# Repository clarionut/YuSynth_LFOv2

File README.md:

# YuSynth_LFOv2

My modifications to the [YuSynth LFO version #2](http://yusynth.net/Modular/EN/LFO/VC-LFO2.html).

Alterations include
- changes to some component values to reduce current draw
- an increase in the pulse width range to allow very short (or long) pulses
- a fix for glitches in the pulse wave output at low (< 1-2Hz) frequencies
- a modification of the [fix by Gabbagabi](https://electro-music.com/forum/viewtopic.php?t=69587) for problems adjusting the triangle and sine wave symmetry at both high and low frequency settings
- elimination of the 741 op-amp, replaced by the 'spare' TL074

I recently built a second YuSynth LFOv2 for my DIY modular synthesiser. Having installed ammeters in the synth power supply I've become increasingly conscious of high current draw from some modules, and so modified some of the component values to help reduce this, possibly at the expense of some loss of linearity in the control potentiometers (though I haven't noticed this). I also wanted to be able to produce much shorter pulses than the 20-80% duty cycle range of the original. In both of these modules I eliminated the 741 in the rate/modulation input circuitry, instead using the spare op-amp in one of the TL074s (IC3a in the original circuit).

I found that both modules suffered the problem that it was impossible to set the sine and triangle wave symmetry for both the fast and slow speed settings (selected by switching between two different capacitor values). I eventually found the very clever solution by Gabbagabi on the electro-music.com forum (link above). This allows the gain of the fast and slow settings to be adjusted independently, allowing the symmetry to be adjusted for both speed settings. I fixed both my LFOs using a small daughter board for the extra components. The schematic and proposed PCB layout include these in the design, but do note that I have NOT built an LFO using this exact board layout - please check it carefully if you decide to use it!

An additional issue encountered using the pulse wave output as a sequencer clock was that at low frequencies (less that 1-2Hz) the sequencer would occasionally skip steps. Checking the output on a 'scope showed noise pulses at the start of the high phase of the pulse as the comparator (IC2c in the YuSynth original, U2D in my schematic) switched. Adding a high value positive feedback resistor on this comparator gave very clean switching and no more skipped steps from the sequencer.

The original YuSynth schematic includes a ramp (inverted sawtooth) output via R18 (on the YuSynth schematic, R24 here). I included this output on my PCB design, but didn't connect it to the panel. It is available if required though.

This is the new procedure for trimming the triangle/sine wave outputs:
- switch the LFO to the FAST (x1) setting
- monitor the TRIANGLE output with a 'scope
- adjust the FAST SAW BIAS trimmer to get a good symmetrical triangle wave
- adjust the SINE/TRI SYM trimmer to remove any DC offset
- check the SINE output is also symmetrical at this point
- switch the LFO to the SLOW (x10) setting and monitor the triangle output
- iteratively adjust the SLOW SAW BIAS and SLOW GAIN trimmers to get a good triangle wave with no DC offset. These trimmers interact with each other, so make small adjustments to be sure you're going the right way. Do NOT touch the SINE/TRI SYM trimmer during this process.

If there's an extreme imbalance between the FAST and SLOW settings you may need to adjust the value of R18 as well.

The kiCad schematic and PCB design use some custom symbols and footprints, so you may need to include the contents of my [kiCad_libraries repository](https://github.com/clarionut/kiCad_libraries).

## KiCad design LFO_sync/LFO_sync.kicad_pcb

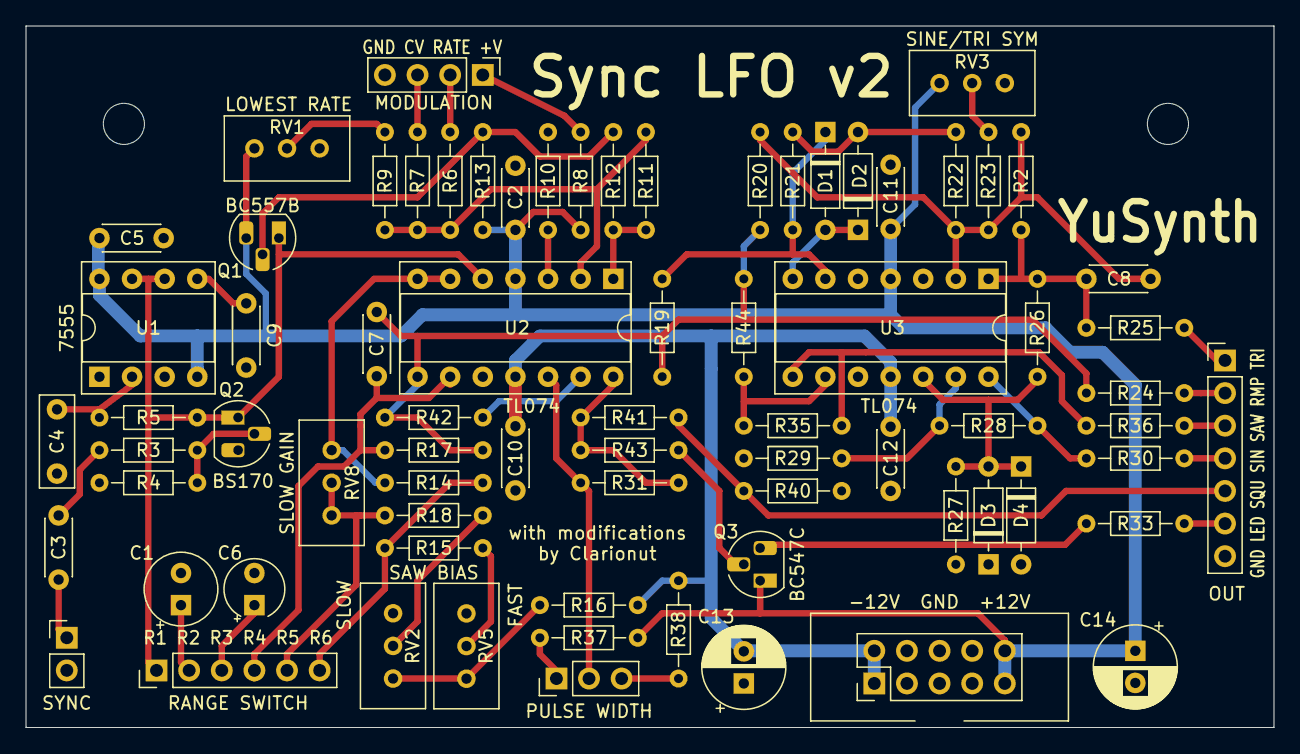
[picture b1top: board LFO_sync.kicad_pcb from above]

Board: 2 copper layers, 97.2 x 54.6 mm, 75 parts (0 on the bottom side), 51 nets.

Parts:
C1: 10u; CP_Radial_Tantal_D5.5mm_P2.50mm
C2, C5, C10, C11, C12: 100n; C_Disc_D4.3mm_W1.9mm_P5.00mm
C3, C9: 10n; C_Disc_D4.3mm_W1.9mm_P5.00mm
C4: 47n; C_Rect_L7.0mm_W2.5mm_P5.00mm
C6: 1u; CP_Radial_Tantal_D4.5mm_P2.50mm
C7: 120p; C_Disc_D4.3mm_W1.9mm_P5.00mm
C8: 1n; C_Disc_D4.3mm_W1.9mm_P5.00mm
C13, C14: 10u; CP_Radial_D6.3mm_P2.50mm
D1, D2, D3, D4: 1N4148; D_DO-35_SOD27_P7.62mm_Horizontal
J1: MODULATION; PinHeader_1x04_P2.54mm_Vertical
J2: SYNC; PinHeader_1x02_P2.54mm_Vertical
J3: RANGE; PinHeader_1x06_P2.54mm_Vertical
J4: PULSE WIDTH; PinHeader_1x03_P2.54mm_Vertical
J7: OUTPUTS; PinHeader_1x07_P2.54mm_Vertical
J8: POWER; Power_2x05
Q1: BC557B; TO-92_HandSolder
Q2: BS170; TO-92_HandSolder
Q3: BC547C; TO-92_HandSolder
R2: 200k; R_Axial_DIN0204_L3.6mm_D1.6mm_P7.62mm_Horizontal
R3, R41, R42: 10k; R_Axial_DIN0204_L3.6mm_D1.6mm_P7.62mm_Horizontal
R4, R6, R7, R9, R11, R14, R15, R19, R20, R21, R33, R35, R44: 100k; R_Axial_DIN0204_L3.6mm_D1.6mm_P7.62mm_Horizontal
R5, R24, R25, R36: 1k; R_Axial_DIN0204_L3.6mm_D1.6mm_P7.62mm_Horizontal
R8: 12k; R_Axial_DIN0204_L3.6mm_D1.6mm_P7.62mm_Horizontal
R10: 8k2; R_Axial_DIN0204_L3.6mm_D1.6mm_P7.62mm_Horizontal
R12, R16: 27k; R_Axial_DIN0204_L3.6mm_D1.6mm_P7.62mm_Horizontal
R13: 820R; R_Axial_DIN0204_L3.6mm_D1.6mm_P7.62mm_Horizontal
R17, R23, R26: 150k; R_Axial_DIN0204_L3.6mm_D1.6mm_P7.62mm_Horizontal
R18, R43: 47k; R_Axial_DIN0204_L3.6mm_D1.6mm_P7.62mm_Horizontal
R22: 50k; R_Axial_DIN0204_L3.6mm_D1.6mm_P7.62mm_Horizontal
R27: 22k; R_Axial_DIN0204_L3.6mm_D1.6mm_P7.62mm_Horizontal
R28: 15k; R_Axial_DIN0204_L3.6mm_D1.6mm_P7.62mm_Horizontal
R29: 1k5; R_Axial_DIN0204_L3.6mm_D1.6mm_P7.62mm_Horizontal
R30: 470R; R_Axial_DIN0204_L3.6mm_D1.6mm_P7.62mm_Horizontal
R31: 3M3; R_Axial_DIN0204_L3.6mm_D1.6mm_P7.62mm_Horizontal
R37, R38: 56k; R_Axial_DIN0204_L3.6mm_D1.6mm_P7.62mm_Horizontal
R40: 7k5; R_Axial_DIN0204_L3.6mm_D1.6mm_P7.62mm_Horizontal
RV1, RV3: 50k; Potentiometer_Bourns_3296W_Vertical
RV2, RV5, RV8: 100k; Potentiometer_Bourns_3296W_Vertical
U1: ICM7555xP; DIP-8_W7.62mm_Socket
U2, U3: TL074; DIP-14_W7.62mm_Socket

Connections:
+12V: C2.1, C5.2, C11.2, C14.1, J8.9, J8.10, Q1.3 (E), Q3.1 (C), R8.1, R13.1, R37.1, RV1.3, RV3.1, U1.4 (R), U1.8 (VCC), U2.4 (V+), U3.4 (V+)
-12V: C10.1, C12.2, C13.2, J8.1, J8.2, R16.1, R38.1, U2.11 (V-), U3.11 (V-)
/+V_RATE: J1.1, R8.2
/CV_MOD: J1.3, R7.2
/LED: J7.6, R33.1
/PULSE: J7.5, R40.1, R41.1
/PW1: J4.1, R37.2
/PW2: J4.2, R31.2, U2.12 (+)
/PW3: J4.3, R38.2
/R1: J3.1, Q1.1 (C), Q2.1 (D), R5.2, U1.6 (THR), U1.7 (DIS), U2.5 (+)
/R2: C1.1, J3.2
/R3: C6.1, J3.3
/R4: C7.2, J3.4, R17.2, U2.9 (-)
/R5: J3.6, R14.2, R15.2
/R6: J3.5, R18.2, RV8.2, RV8.3
/RAMP: J7.2, R24.1
/RATE: J1.2, R6.2
/SAW: J7.3, R36.1
/SINE: J7.4, R30.1
/SYNC: C3.2, J2.1
/TRI: J7.1, R25.1
GND: C1.2, C2.2, C4.2, C5.1, C6.2, C9.2, C10.2, C11.1, C12.1, C13.1, C14.2, D3.1 (K), D4.2 (A), J1.4, J2.2, J7.7, J8.3, J8.4, J8.5, J8.6, J8.7, J8.8, Q2.3 (S), R4.2, R10.2, R27.2, R29.2, R40.2, RV1.1, RV2.3, RV3.3, RV5.3, U1.1 (GND), U2.10 (+), U3.3 (+), U3.5 (+), U3.10 (+)
unnamed: C3.1, R3.2
unnamed: C7.1, R17.1, R19.2, R20.2, R24.2, R42.2, R44.2, U2.8
unnamed: C8.1, R2.1, R25.2, R26.2, U3.1
unnamed: D1.2 (A), D2.1 (K), U3.7
unnamed: D1.1 (K), R19.1, R21.2, U3.6 (-)
unnamed: D2.2 (A), R21.1, R22.1
unnamed: D3.2 (A), D4.1 (K), R26.1, R27.1, U3.12 (+)
unnamed: Q1.2 (B), R12.1, R13.2
unnamed: Q2.2 (G), R3.1, R4.1
unnamed: Q3.2 (B), R43.1
unnamed: Q3.3 (E), R33.2
unnamed: R9.1, RV1.2
unnamed: R11.1, R12.2, U2.1
unnamed: R15.1, RV5.2
unnamed: R16.2, RV2.1, RV5.1
unnamed: R18.1, RV2.2
unnamed: R23.1, RV3.2
unnamed: R28.1, R30.2, U3.14
unnamed: R31.1, R41.2, R43.2, U2.14
unnamed: R35.1, R36.2, U3.8
unnamed: C9.1, U1.5 (CV)
unnamed: C4.1, R5.1, U1.2 (TR)
unnamed: R10.1, U2.3 (+)
unnamed: R6.1, R7.1, R9.2, R11.2, U2.2 (-)
unnamed: R14.1, RV8.1, U2.6 (-), U2.7
unnamed: R42.1, U2.13 (-)
unnamed: C8.2, R2.2, R20.1, R22.2, R23.2, U3.2 (-)
unnamed: R35.2, R44.1, U3.9 (-)
unnamed: R28.2, R29.1, U3.13 (-)

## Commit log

2024-07-02 Update README.md
    My modifications to the YuSynth LFO version #2 (http://yusynth.net/Modular/EN/LFO/VC-LFO2.html).
    Alterations include
    - changes to some component values to reduce current draw
    - an increase in the pulse width range to allow very short (or long) pulses
    - a fix for glitches in the pulse wave output at low (< 1-2Hz) frequencies
    - a modification of the fix by Gabbagabi (https://electro-music.com/forum/viewtopic.php?t=69587) for problems adjusting the triangle and sine wave symmetry at both high and low frequency settings
2024-07-02 Create temp
